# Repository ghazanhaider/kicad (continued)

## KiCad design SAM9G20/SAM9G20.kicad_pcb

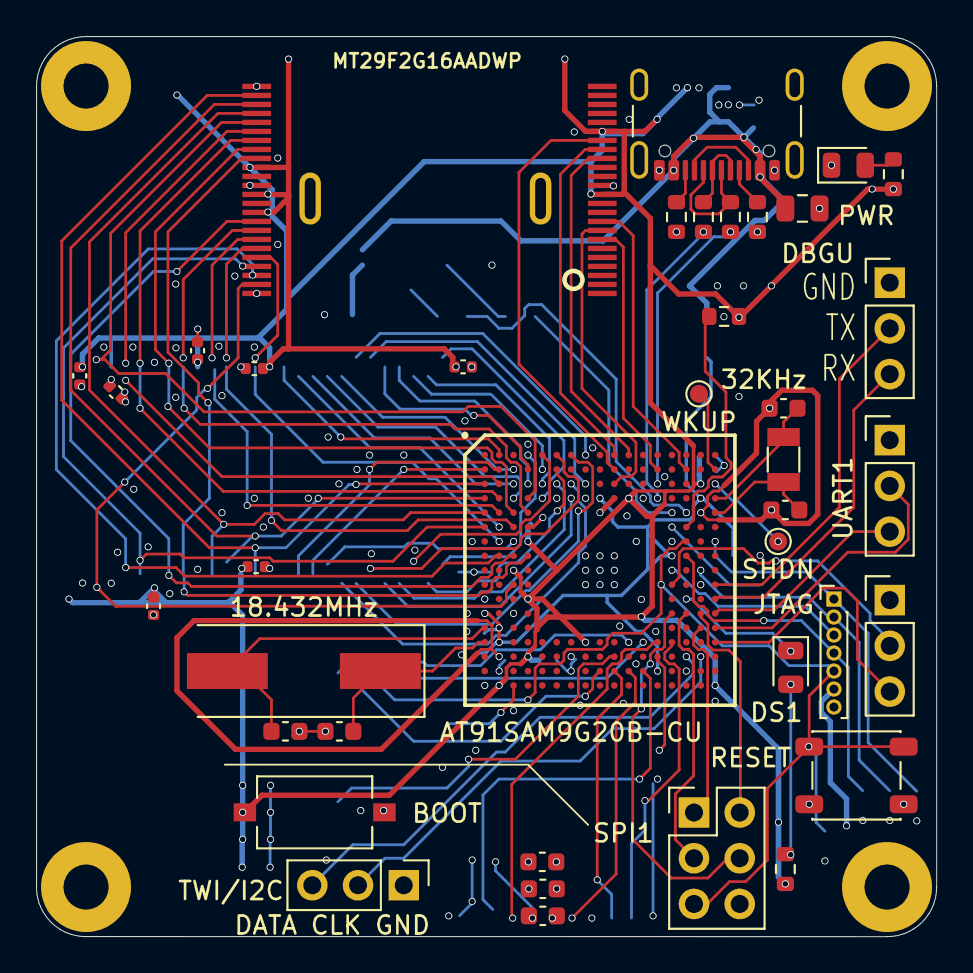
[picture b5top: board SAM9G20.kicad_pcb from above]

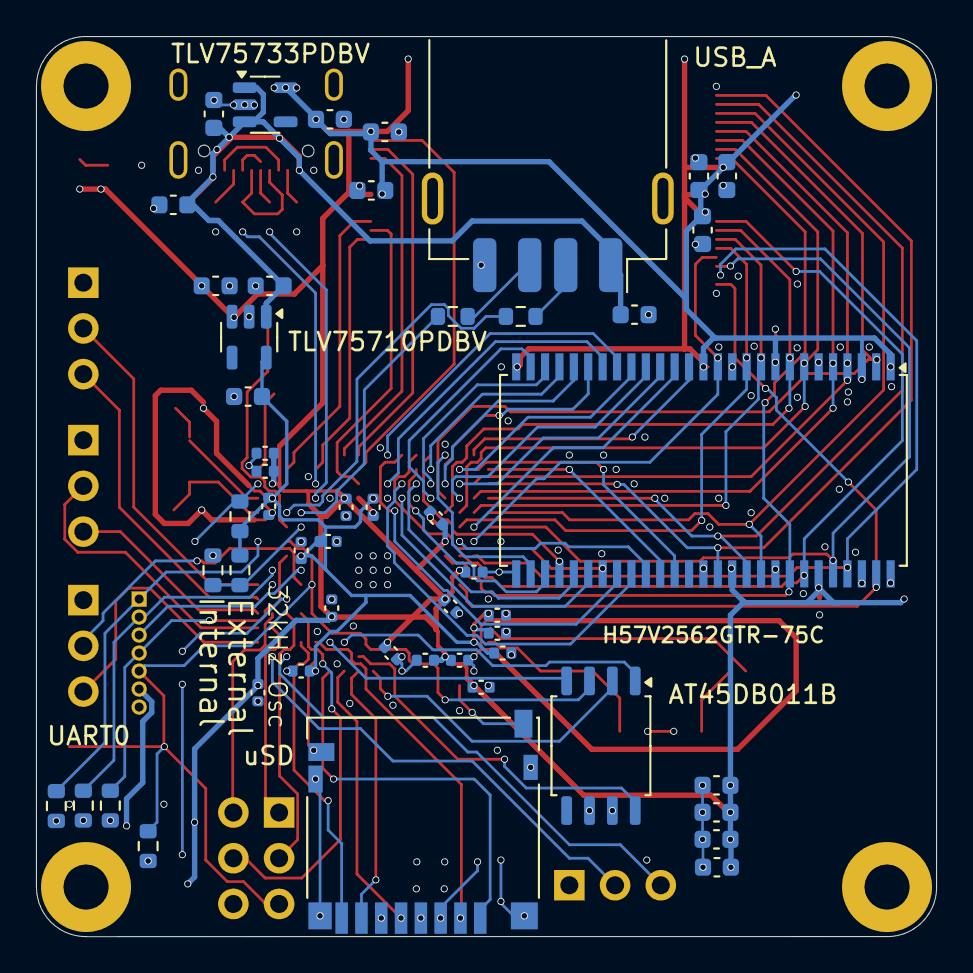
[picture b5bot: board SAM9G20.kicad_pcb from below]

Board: 4 copper layers, 50.0 x 50.0 mm, 94 parts (51 on the bottom side), 99 nets.

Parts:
C1, C2, C3, C4: 10pF; C_0603_1608Metric
C5, C6, C7, C8, C9, C10, C11, C12, C13, C14, C15, C16, C17, C18, C19, C33, C34, C35, C36, C37, C38, C39, C45: 100nF; C_0402_1005Metric
C20, C21, C22, C23: 10uF; C_0402_1005Metric
C24, C25: 1uF; C_0603_1608Metric
C26, C27: 10uF; C_0603_1608Metric
C28: 10nF; C_0603_1608Metric
C29: 47uF; C_0805_2012Metric
C30, C40, C41, C42, C43, C44, C47, C48, C49, C50, C52, C53: 100nF; C_0603_1608Metric
C31, C54: 4.7uF; C_0603_1608Metric
D1: PWR; LED_0805_2012Metric
D2: DS1; LED_0805_2012Metric
H1, H2, H3, H4: MountingHole_Pad; MountingHole_2.5mm_Pad
IC1: AT91SAM9G20B-CU; BGA217C80P17X17_1500X1500X140
J1: USB_A; USB_A_Receptacle_GCT_USB1046
J3: USB Device and Power; USB_C_Receptacle_GCT_USB4105-xx-A_16P_TopMnt_Horizontal
J4: DBGU; PinHeader_1x03_P2.54mm_Vertical
J5: uSD; microSD_HC_Hirose_DM3D-SF
J6: UART1; PinHeader_1x03_P2.54mm_Vertical
J7: UART0; PinHeader_1x03_P2.54mm_Vertical
J9: SPI1; PinHeader_2x03_P2.54mm_Vertical
J10: TWI/I2C; PinHeader_1x03_P2.54mm_Vertical
R1, R2, R3, R4: 27R; R_0603_1608Metric
R7, R10, R18: 1K; R_0603_1608Metric
R8: 470K; R_0603_1608Metric
R9, R14, R15, R16, R17: 100K; R_0603_1608Metric
R11: DNP; R_0603_1608Metric
R12, R13: 5.1K; R_0603_1608Metric
SW1: BOOT; SW_Tactile_SPST_NO_Straight_CK_PTS636Sx25SMTRLFS
SW3: RESET; SW_SPST_PTS647_Sx38
TP1: WKUP; TestPoint_Pad_D1.0mm
TP2: SHDN; TestPoint_Pad_D1.0mm
U1: H57V2562GTR-75C; TSOP-II-54_22.2x10.16mm_P0.8mm
U2: MT29F2G16AADWP; TSOP-48
U3: JTAG; PinHeader_1x07_P1.00mm_Vertical
U4: AT45DB011B; SOIC-8_5.275x5.275mm_P1.27mm
U5: TLV75710PDBV; SOT-23-5
U6: TLV75733PDBV; SOT-23-5
Y1: 18.432MHz; Crystal_SMD_HC49-SD
Y2: 32KHz; Crystal_SMD_3215-2Pin_3.2x1.5mm

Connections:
1.0V: C5.1, C6.1, C7.1, C8.1, C9.1, C10.1, C11.1, C20.1, C26.2, IC1.D9 (VDDCORE_1), IC1.D16 (VDDBU), IC1.H14 (VDDCORE_2), IC1.M1 (VDDCORE_3), IC1.N2 (VDDPLL_1), IC1.P2 (VDDPLL_2), IC1.T13 (VDDCORE_4), R8.2, R14.2, U5.5 (OUT)
3.3V: C12.1, C13.1, C14.1, C15.1, C16.1, C17.1, C18.1, C19.1, C21.1, C22.1, C23.1, C27.2, C28.2, C33.1, C34.1, C35.1, C36.1, C37.1, C38.1, C39.1, C40.1, C41.1, C42.1, C43.1, C44.1, C45.1, C47.1, C48.1, C49.1, C50.1, C52.1, C53.1, C54.1, IC1.C16 (VDDUSB), IC1.D11 (VDDIOM_1), IC1.G4 (VDDIOM_2), IC1.J3 (VDDIOM_3), IC1.L4 (VDDOSC), IC1.P8 (VDDIOP_1), IC1.R4 (VDDANA), IC1.U2 (ADVREF), IC1.U17 (VDDIOP_2), J5.4 (VDD), R7.2, R9.2, R10.2, R15.2, R16.2, R17.2, R18.2, SW1.1 (A), U1.1 (VDD), U1.3 (VDDQ), U1.9 (VDDQ), U1.14 (VDD), U1.27 (VDD), U1.43 (VDDQ), U1.49 (VDDQ), U2.12 (VCC), U2.19 (~WP), U2.34 (VCC@1), U2.37 (VCC@2), U2.39 (VCC@3), U3.6, U5.3 (EN), U6.5 (OUT)
A2: IC1.C4 (A2), U1.23 (A0)
A3: IC1.B5 (A3), U1.24 (A1)
A4: IC1.C5 (A4), U1.25 (A2)
A5: IC1.D5 (A5), U1.26 (A3)
A6: IC1.A4 (A6), U1.29 (A4)
A7: IC1.B6 (A7), U1.30 (A5)
A8: IC1.A5 (A8), U1.31 (A6)
A9: IC1.C6 (A9), U1.32 (A7)
A10: IC1.D7 (A10), U1.33 (A8)
A11: IC1.A6 (A11), U1.34 (A9)
A13: IC1.A7 (A13), U1.35 (A11)
A14: IC1.C7 (A14), U1.36 (A12)
A21: IC1.A10 (A21), U2.17 (ALE)
A22: IC1.A11 (A22), U2.16 (CLE)
BA0/A16: IC1.A8 (BA0/A16), U1.20 (BA0)
BA1/A17: IC1.C8 (BA1/A17), U1.21 (BA1)
BMS: IC1.F15 (BMS), R9.1
CAS: IC1.C3 (CAS), U1.17 (~CAS)
CFIOR/NBS1/NWR1: IC1.B2 (CFIOR/NBS1/NWR1), U1.39 (DQMH)
D0: IC1.D4 (D0), U1.2 (DQ0), U2.29 (I/O_0)
D1: IC1.C2 (D1), U1.4 (DQ1), U2.30 (I/O_1)
D2: IC1.D2, U1.5 (DQ2), U2.31 (I/O_2)
D3: IC1.E3 (D3), U1.7 (DQ3), U2.32 (I/O_3)
D4: IC1.E4 (D4), U1.8 (DQ4), U2.41 (I/O_4)
D5: IC1.E2 (D5), U1.10 (DQ5), U2.42 (I/O_5)
D6: IC1.F3 (D6), U1.11 (DQ6), U2.43 (I/O_6)
D7: IC1.G2 (D7), U1.13 (DQ7), U2.44 (I/O_7)
D8: IC1.C1 (D8), U1.42 (DQ8), U2.26 (I/O_8)
D9: IC1.D1 (D9), U1.44 (DQ9), U2.27 (I/O_9)
D10: IC1.E1 (D10), U1.45 (DQ10), U2.28 (I/O_10)
D11: IC1.H4 (D11), U1.47 (DQ11), U2.33 (I/O_11)
D12: IC1.H3 (D12), U1.48 (DQ12), U2.40 (I/O_12)
D13: IC1.F1 (D13), U1.50 (DQ13), U2.45 (I/O_13)
D14: IC1.H2 (D14), U1.51 (DQ14), U2.46 (I/O_14)
D15: IC1.K3 (D15), U1.53 (DQ15), U2.47 (I/O_15)
DDM: IC1.D13 (DDM), R1.2
DDP: IC1.C13 (DDP), R2.2
DRXD: IC1.L17 (PB14), J4.3
DTXD: IC1.K17 (PB15), J4.2
GNDANA: C1.2, C2.2, C3.2, C4.2, C5.2, C6.2, C7.2, C8.2, C9.2, C10.2, C11.2, C12.2, C13.2, C14.2, C15.2, C16.2, C17.2, C18.2, C19.2, C20.2, C21.2, C22.2, C23.2, C24.1, C25.1, C26.1, C27.1, C28.1, C29.1, C30.1, C31.1, C33.2, C34.2, C35.2, C36.2, C37.2, C38.2, C39.2, C40.2, C41.2, C42.2, C43.2, C44.2, C45.2, C47.2, C48.2, C49.2, C50.2, C52.2, C53.2, C54.2, D1.1 (K), H1.1, H2.1, H3.1, H4.1, IC1.D6 (GND_1), IC1.D8 (GND_2), IC1.D10 (GNDUSB_1), IC1.D12 (GNDUSB_2), IC1.E16 (GNDBU), IC1.F4 (GND_3), IC1.G14 (GND_4), IC1.H8 (GND_5), IC1.H9 (GND_6), IC1.H10 (GND_7), IC1.J8 (GND_8), IC1.J9 (GND_9), IC1.J10 (GND_10), IC1.K8 (GND_11), IC1.K9 (GND_12), IC1.K10 (GND_13), IC1.K16 (GND_14), IC1.L1 (GND_15), IC1.M3 (GND_16), IC1.R2 (GNDANA), IC1.R7 (GND_17), IC1.T2 (GNDPLL_1), IC1.T7 (GND_18), IC1.T15 (GND_19), IC1.U1 (GNDPLL_2), J1.4 (GND), J1.5 (Shield), J3.A1 (GND), J3.A12 (GND), J3.B1 (GND), J3.B12 (GND), J3.S1 (SHIELD), J4.1, J5.3 (VSS), J5.6 (VSS), J5.11 (WRITE_PROTECT), J6.1, J7.1, J9.6, J10.1, R11.2, R12.2, R13.2, SW3.2, U1.6 (VSSQ), U1.12 (VSSQ), U1.28 (VSS), U1.41 (VSS), U1.46 (VSSQ), U1.52 (VSSQ), U1.54 (VSS), U2.13 (VSS), U2.25 (VSS@1), U2.36 (VSS@2), U2.48 (VSS@3), U3.7, U4.7 (GND), U5.2 (GND), U6.2 (GND)
HDMA: IC1.E15 (HDMA), R4.2
HDPA: IC1.E14 (HDPA), R3.2
MCCDA: IC1.P13 (PA7), J5.2 (CMD)
MCCK: IC1.T11 (PA8), J5.5 (CLK)
MCDA0: IC1.T10 (PA6), J5.7 (DAT0)
MCDA1: IC1.P14 (PA9), J5.8 (DAT1)
MCDA2: IC1.R13 (PA10), J5.9 (DAT2)
MCDA3: IC1.T12 (PA11), J5.1 (CD/DAT3)
NANDOE: IC1.C10 (NANDOE), U2.8 (~RE)
NANDWE: IC1.B10 (NANDWE), U2.18 (~WE)
NBS0/A0: IC1.A2 (NBS0/A0), U1.15 (DQML)
NRST: IC1.G15 (NRST), J9.5, R10.1, SW3.1, U3.5, U4.3 (~RESET)
unnamed: D1.2 (A), R7.1
unnamed: D2.2 (A), R18.1
unnamed: J1.3 (D+), R3.1
unnamed: J1.2 (D-), R4.1
unnamed: J3.A5 (CC1), R12.1
unnamed: J3.B5 (CC2), R13.1
unnamed: J3.A6 (D+), J3.B6 (D+), R2.1
unnamed: J3.A7 (D-), J3.B7 (D-), R1.1
unnamed: SW1.2 (B), U4.6 (VCC)
OSCSEL: IC1.F14 (OSCSEL), R11.1, R14.1
PA0: IC1.R10 (PA0), U4.8 (SO)
PA1: IC1.P11 (PA1), U4.1 (SI)
PA2: IC1.T9 (PA2), U4.2 (SCK)
PA3: IC1.P12 (PA3), U4.4 (~CS)
PA23: IC1.R15 (PA23), J10.3
PA24: IC1.R16 (PA24), J10.2
PB0: IC1.N16 (PB0), J9.1
PB1: IC1.M14 (PB1), J9.4
PB2: IC1.M15 (PB2), J9.3
PB3: IC1.M16 (PB3), J9.2
PB4: IC1.K14 (PB4), J7.2
PB5: IC1.P17 (PB5), J7.3
PB6: IC1.N17 (PB6), J6.2
PB7: IC1.M17 (PB7), J6.3
PB9: D2.1 (K), IC1.L15 (PB9)
PC2: IC1.U3 (PC2), J5.10 (CARD_DETECT)
PC13: IC1.B13 (PC13), U2.7 (~R/B)
PC14: IC1.B15 (PC14), U2.9 (~CE)
RAS: IC1.D3 (RAS), U1.18 (~RAS)
SDA10: IC1.B4 (SDA10), U1.22 (A10)
SDCK: IC1.B1 (SDCK), U1.38 (CLK)
SDCKE: IC1.G3 (SDCKE), U1.37 (CKE)
SDCS/NCS1: IC1.B3 (SDCS/NCS1), U1.19 (~CS)
SDWE: IC1.F2 (SDWE), U1.16 (~WE)
SHDN: IC1.C17 (SHDN), R8.1, TP2.1
TCK: IC1.H15 (TCK), R17.1, U3.4
TDI: IC1.J16 (TDI), R16.1, U3.2
TDO: IC1.J14 (TDO), U3.3
TMS: IC1.G17 (TMS), R15.1, U3.1
VBUS: C24.2, C25.2, C29.2, C30.2, C31.2, J1.1 (VBUS), J3.A4 (VBUS), J3.A9 (VBUS), J3.B4 (VBUS), J3.B9 (VBUS), U5.1 (IN), U6.1 (IN), U6.3 (EN)
WKUP: IC1.B17 (WKUP), TP1.1
XIN: C1.1, IC1.N1 (XIN), Y1.2
XIN32: C3.1, IC1.D17 (XIN32), Y2.2
XOUT: C2.1, IC1.P1 (XOUT), Y1.1
XOUT32: C4.1, IC1.E17 (XOUT32), Y2.1

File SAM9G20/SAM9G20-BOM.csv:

Reference,Value,Datasheet,Footprint,Qty,DNP,,
U3,JTAG,~,,1,,,
SW3,RESET,~,Button_Switch_SMD:SW_SPST_PTS647_Sx38,1,,,
SW1,BOOT,~,Button_Switch_SMD:SW_Tactile_SPST_NO_Straight_CK_PTS636Sx25SMTRLFS,1,,KSR221GNCLFS,
"C5,C6,C7,C8,C9,C10,C11,C12,C13,C14,C15,C16,C17,C18,C19,C33,C34,C35,C36,C37,C38,C39,C45",100nF,~,Capacitor_SMD:C_0402_1005Metric,23,,,
"C20,C21,C22,C23",10uF,~,Capacitor_SMD:C_0402_1005Metric,4,,,
"C1,C2,C3,C4",10pF,~,Capacitor_SMD:C_0603_1608Metric,4,,only 9,100
"C24,C25",1uF,~,Capacitor_SMD:C_0603_1608Metric,2,,,
"C26,C27",10uF,~,Capacitor_SMD:C_0603_1608Metric,2,,,100
C28,10nF,~,Capacitor_SMD:C_0603_1608Metric,1,,,
"C30,C40,C41,C42,C43,C44,C47,C48,C49,C50,C52,C53",100nF,~,Capacitor_SMD:C_0603_1608Metric,12,,only 23,100
"C31,C54",4.7uF,~,Capacitor_SMD:C_0603_1608Metric,2,,,
C29,47uF,~,Capacitor_SMD:C_0805_2012Metric,1,,only 7 found,
J5,SD_Card_Receptacle,http://portal.fciconnect.com/Comergent//fci/drawing/10067847.pdf,Connector_Card:microSD_HC_Hirose_DM3D-SF,1,,only 3 found,10
J4,DBGU,~,Connector_PinHeader_2.54mm:PinHeader_1x03_P2.54mm_Vertical,1,,,
J6,UART1,~,Connector_PinHeader_2.54mm:PinHeader_1x03_P2.54mm_Vertical,1,,,
J7,UART0,~,Connector_PinHeader_2.54mm:PinHeader_1x03_P2.54mm_Vertical,1,,,
J10,TWI,~,Connector_PinHeader_2.54mm:PinHeader_1x03_P2.54mm_Vertical,1,,,
J9,SPI1,~,Connector_PinHeader_2.54mm:PinHeader_2x03_P2.54mm_Vertical,1,,,
J1,USB_A,~,Connector_USB:USB_A_Receptacle_GCT_USB1046,1,,only 3 found,
J3,USB Device and Power,https://www.usb.org/sites/default/files/documents/usb_type-c.zip,Connector_USB:USB_C_Receptacle_GCT_USB4105-xx-A_16P_TopMnt_Horizontal,1,,,10
Y2,32.768kHz,ECS-.327-12.5-34B-TR,Crystal:Crystal_SMD_3215-2Pin_3.2x1.5mm,1,,,
Y1,18.432MHz,ABLS-18.432MHZ-B2-T,Crystal:Crystal_SMD_HC49-SD,1,,,
IC1,AT91SAM9G20B-CU,http://www.microchip.com/mymicrochip/filehandler.aspx?ddocna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,GhazanCustom:BGA217C80P17X17_1500X1500X140,1,,,
U2,MT29F2G16AADWP,,GhazanCustom:TSOP-48,1,,only 5,
D1,PWR,LTST-S220GKT,LED_SMD:LED_0805_2012Metric,1,,,
D2,DS1,LTST-S220GKT,LED_SMD:LED_0805_2012Metric,1,,,
U4,AT45DB011B-SU,,Package_SO:SOIC-8_5.275x5.275mm_P1.27mm,1,,,
U1,H57V2562GTR-75C,,Package_SO:TSOP-II-54_22.2x10.16mm_P0.8mm,1,,,
U5,TLV75710PDBV,https://www.ti.com/lit/ds/symlink/tlv757p.pdf,Package_TO_SOT_SMD:SOT-23-5,1,,,
U6,TLV75733PDBV,https://www.ti.com/lit/ds/symlink/tlv757p.pdf,Package_TO_SOT_SMD:SOT-23-5,1,,,
"R1,R2,R3,R4",27R,~,Resistor_SMD:R_0603_1608Metric,4,,,100
"R7,R10,R18",1K,~,Resistor_SMD:R_0603_1608Metric,3,,,100
R8,470K,~,Resistor_SMD:R_0603_1608Metric,1,,,
"R9,R14,R15,R16,R17",100K,~,Resistor_SMD:R_0603_1608Metric,5,,,
R11,DNP,~,Resistor_SMD:R_0603_1608Metric,1,,,
"R12,R13",5.1K,~,Resistor_SMD:R_0603_1608Metric,2,,,
TP1,WKUP,~,TestPoint:TestPoint_Pad_D1.0mm,1,,,
TP2,SHDN,~,TestPoint:TestPoint_Pad_D1.0mm,1,,,

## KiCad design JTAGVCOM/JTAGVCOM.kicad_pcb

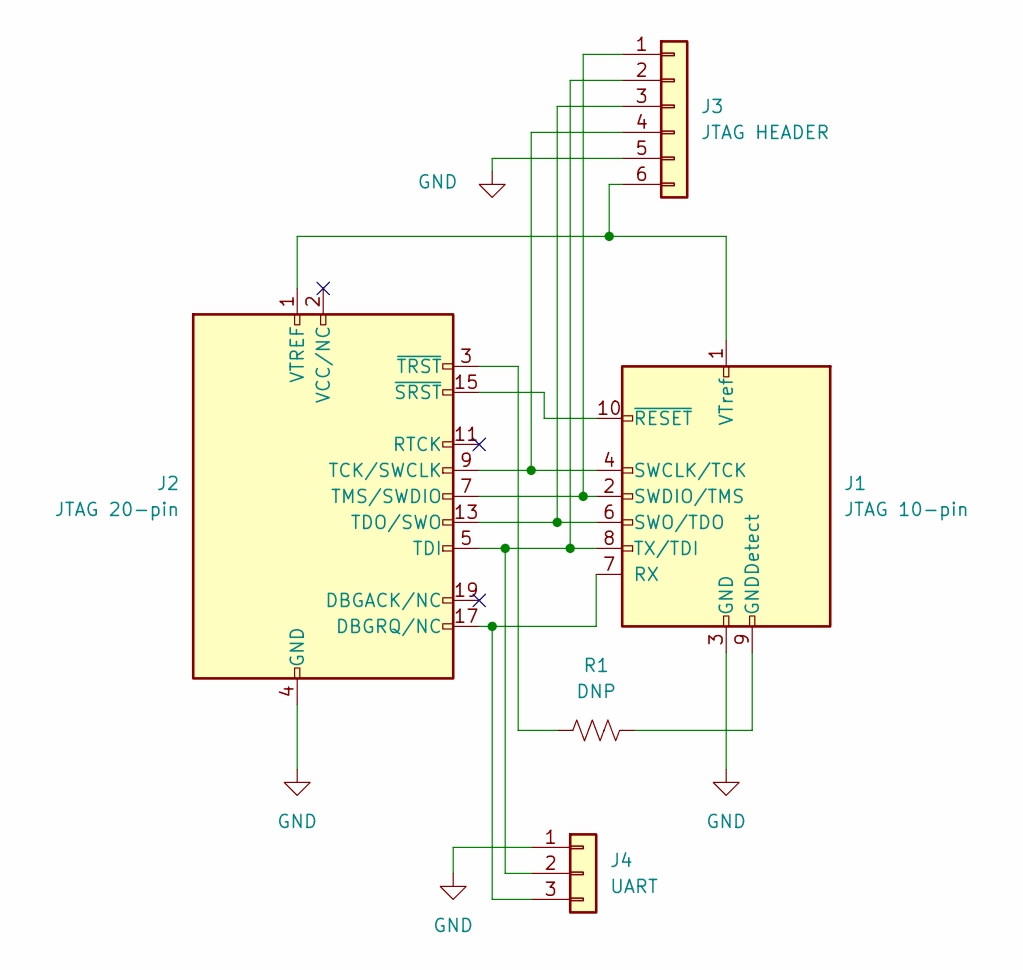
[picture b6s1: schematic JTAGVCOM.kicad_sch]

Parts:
J1: JTAG 10-pin; PinHeader_2x05_P1.27mm_Vertical
J2: JTAG 20-pin; PinHeader_2x10_P2.54mm_Vertical
J3: JTAG HEADER; PinHeader_1x06_P2.54mm_Vertical
J4: UART; PinHeader_1x03_P2.54mm_Vertical
R1: DNP; R_0805_2012Metric_Pad1.20x1.40mm_HandSolder

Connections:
GND: J1.3 (GND), J1.5 (GND), J2.4 (GND), J2.6 (GND), J2.8 (GND), J2.10 (GND), J2.12 (GND), J2.14 (GND), J2.16 (GND), J2.18 (GND), J2.20 (GND), J3.5, J4.1
unnamed: J1.9 (GNDDetect), R1.2
unnamed: J1.7 (RX), J2.17 (DBGRQ/NC), J4.3
unnamed: J1.4 (SWCLK/TCK), J2.9 (TCK/SWCLK), J3.4
unnamed: J1.2 (SWDIO/TMS), J2.7 (TMS/SWDIO), J3.1
unnamed: J1.6 (SWO/TDO), J2.13 (TDO/SWO), J3.3
unnamed: J1.8 (TX/TDI), J2.5 (TDI), J3.2, J4.2
unnamed: J1.1 (VTref), J2.1 (VTREF), J3.6
unnamed: J1.10 (~RESET), J2.15 (~SRST)
unnamed: J2.3 (~TRST), R1.1

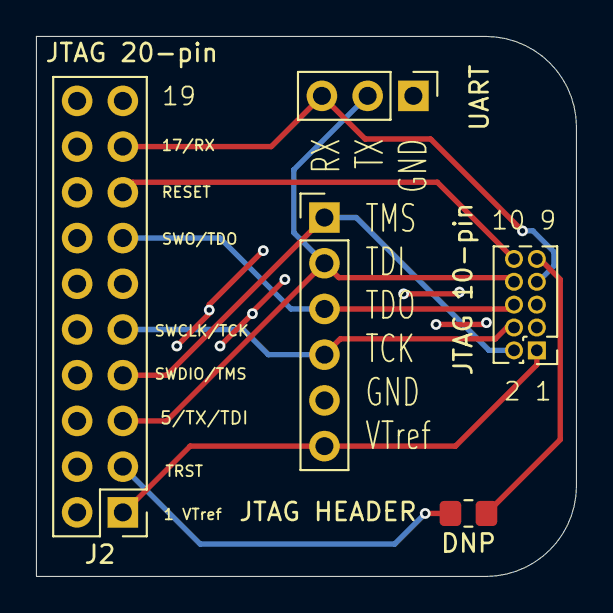
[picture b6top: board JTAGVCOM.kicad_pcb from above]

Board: 2 copper layers, 30.0 x 30.0 mm, 5 parts (0 on the bottom side), 10 nets.

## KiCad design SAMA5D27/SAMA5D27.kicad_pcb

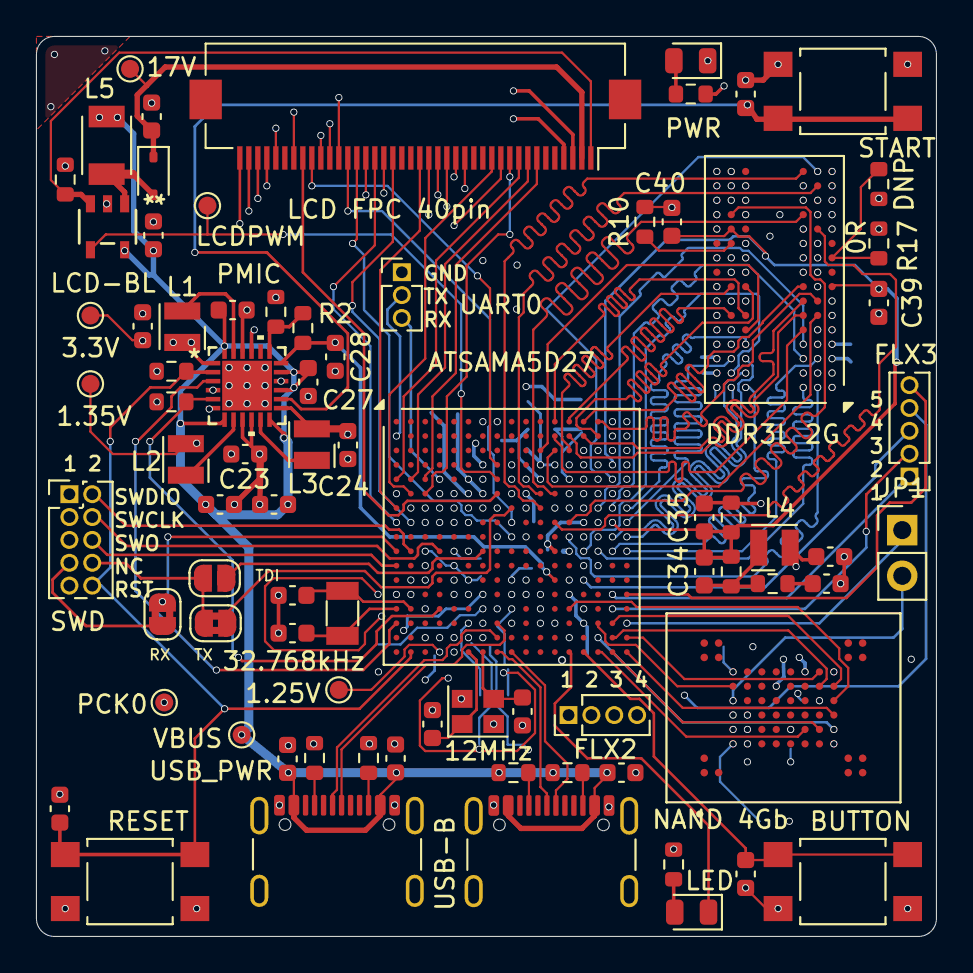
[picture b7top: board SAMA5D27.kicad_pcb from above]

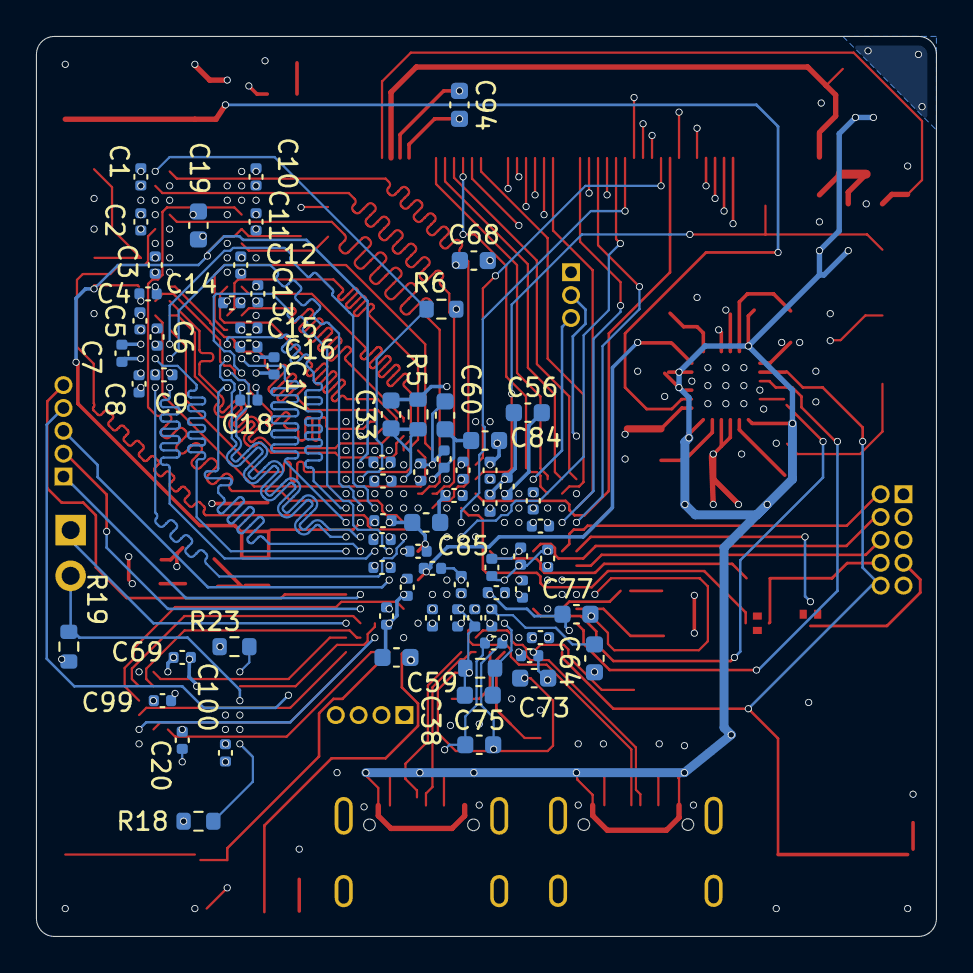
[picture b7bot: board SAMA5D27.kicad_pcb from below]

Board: 6 copper layers, 50.0 x 50.0 mm, 152 parts (73 on the bottom side), 151 nets.

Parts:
C1, C2, C3, C4, C5, C6, C7, C8, C9, C10, C11, C12, C13, C14, C15, C16, C17, C18, C20, C41, C42, C43, C44, C45, C46, C47, C48, C49, C50, C51, C52, C53, C54, C55, C57, C58, C62, C63, C65, C67, C69, C71, C72, C74, C76, C78, C79, C83, C87, C89, C91, C99, C100: 100nF; C_0402_1005Metric
C19, C56, C59, C64, C68, C73, C75, C77, C84, C85, C92, C93: 1uF; C_0603_1608Metric
C21, C23, C24: 22uF; C_0603_1608Metric
C22, C25, C26, C27, C28, C36, C37, C80, C81, C94, C97: 4.7uF; C_0603_1608Metric
C29, C30, C31, C32: 16pF; C_0603_1608Metric
C33: 22pF; C_0603_1608Metric
C34, C35, C39, C40, C95, C96, C98: 100nF; C_0603_1608Metric
C38: 10pF; C_0603_1608Metric
C60: 10nF; C_0603_1608Metric
D1: D_Schottky; D_SOD-323
D2: LED; LED_0805_2012Metric
D3: PWR; LED_0805_2012Metric
IC1: D1216ECMDXGJD-U; Micron_FBGA-96_7.5x13.5mm_Layout9x16_P0.8mm
J1: LCD FPC 40pin; Hirose_FH12-40S-0.5SH_1x40-1MP_P0.50mm_Horizontal
J2: SWD; PinHeader_2x05_P1.27mm_Vertical
J3: UART0; PinHeader_1x03_P1.27mm_Vertical
J5: FLX2; PinHeader_1x04_P1.27mm_Vertical
J6: FLX3; PinHeader_1x05_P1.27mm_Vertical
JP1: BOOT; PinHeader_1x02_P2.54mm_Vertical
JP2: Jumper_2_Small_Open; SolderJumper-2_P1.3mm_Open_RoundedPad1.0x1.5mm
JP3, JP4: Jumper_2_Small_Bridged; SolderJumper-2_P1.3mm_Bridged2Bar_RoundedPad1.0x1.5mm
L1, L2, L3: 2.2uH; L_Wurth_WE-LQSH-2512
L4: 10uH 150mA; L_Wurth_WE-LQSH-2512
L5: 15uH; L_TDK_NLV32_3.2x2.5mm
P1: USB_PWR; USB_C_Receptacle_GCT_USB4105-xx-A_16P_TopMnt_Horizontal
P2: USB-B; USB_C_Receptacle_GCT_USB4105-xx-A_16P_TopMnt_Horizontal
R1: 182k 1%; R_0603_1608Metric
R2: 324k 1%; R_0603_1608Metric
R3, R4, R6: 100k; R_0603_1608Metric
R5: 23.2k 1%; R_0603_1608Metric
R7, R8: 6.8k 1%; R_0603_1608Metric
R9: 1R 1%; R_0603_1608Metric
R10: 240R 1%; R_0603_1608Metric
R11, R12: 5.1k 1%; R_0603_1608Metric
R13, R14: 56k 1%; R_0603_1608Metric
R15: 5.62k 1%; R_0603_1608Metric
R16: DNP; R_0603_1608Metric
R17: 0R; R_0603_1608Metric
R18, R19: 470k; R_0603_1608Metric
R20: 6.3; R_0603_1608Metric
R21, R22, R23: 1k; R_0603_1608Metric
SW1: BUTTON; SW_SPST_TL3305A
SW2: START; SW_SPST_TL3305A
SW3: RESET; SW_SPST_TL3305A
TP1: VBUS; TestPoint_Pad_D1.0mm
TP2: 3.3V; TestPoint_Pad_D1.0mm
TP3: 1.35V; TestPoint_Pad_D1.0mm
TP4: 1.25V; TestPoint_Pad_D1.0mm
TP5: PCK0; TestPoint_Pad_D1.0mm
TP6: 17V; TestPoint_Pad_D1.0mm
TP7: LCDPWM; TestPoint_Pad_D1.0mm
U1: LCD-BL; TSOT-23-5_D5_MCH
U2: PMIC; VQFN24_RMB_MCH
U3: MT29F4G08ABAFAH4-IT:F; BGA63C80P10X12_1050X1300X100N
U5: ATSAMA5D27; LFBGA-289_14x14mm_Layout17x17_P0.8mm
Y1: 12MHz; Crystal_SMD_2520-4Pin_2.5x2.0mm
Y2: 32.768kHz; Crystal_SMD_3215-2Pin_3.2x1.5mm

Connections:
+1V25: C24.2, C48.1, C49.1, C50.1, C51.1, C52.1, C53.1, C62.2, C64.2, C71.1, C72.1, C73.1, C84.1, L3.1, TP4.1, U2.13 (OUT3), U5.D7 (VDDCORE), U5.D9 (VDDCORE), U5.H3 (VDDCORE), U5.K13 (VDDCORE), U5.N5 (VDDCORE), U5.N9 (VDDCORE), U5.P7 (VDDUTMIC), U5.R9 (VDDHSIC), U5.U4 (VDDPLLA)
+2V5: C28.1, C89.1, R2.2, U2.18 (LOUT), U5.M12 (VDDFUSE)
+3V3: C20.2, C21.1, C54.1, C55.1, C56.1, C57.1, C58.1, C59.1, C63.1, C65.2, C67.2, C69.2, C74.1, C75.1, C76.1, C77.1, C78.1, C79.1, C83.1, C85.1, C87.1, C91.2, C94.2, C99.2, C100.2, J1.4, J2.1 (VTref), L1.2, R3.2, R4.2, R18.1, R19.2, R21.1, R22.1, R23.2, TP2.1, U2.1 (OUT1), U2.21 (LEN), U3.D3 (VCC), U3.G4 (VCC), U3.H8 (VCC), U3.J6 (VCC), U5.E6 (VDDIOP0), U5.F4 (VDDISC), U5.F7 (VDDIOP0), U5.F10 (VDDIOP2), U5.K3 (VDDANA), U5.L5 (VDDANA), U5.M6 (ADVREFP), U5.N7 (VDDBU), U5.N13 (VDDIOP1), U5.P8 (VDDUTMII), U5.P11 (VDDSDMMC), U5.R14 (VDDIOP1), U5.T3 (VDDAUDIOPLL), U5.T7 (VDDOSC)
/NAND/NAND_CE: JP1.2 (B), R19.1, U3.C6 (CE#)
DDR_A0: IC1.N3 (A0), U5.F12 (DDR_A0)
DDR_A1: IC1.P7 (A1), U5.C17 (DDR_A1)
DDR_A2: IC1.P3 (A2), U5.B17 (DDR_A2)
DDR_A3: IC1.N2 (A3), U5.B16 (DDR_A3)
DDR_A4: IC1.P8 (A4), U5.C16 (DDR_A4)
DDR_A5: IC1.P2 (A5), U5.G14 (DDR_A5)
DDR_A6: IC1.R8 (A6), U5.F14 (DDR_A6)
DDR_A7: IC1.R2 (A7), U5.F11 (DDR_A7)
DDR_A8: IC1.T8 (A8), U5.C14 (DDR_A8)
DDR_A9: IC1.R3 (A9), U5.D13 (DDR_A9)
DDR_A10: IC1.L7 (A10/AP), U5.C15 (DDR_A10)
DDR_A11: IC1.R7 (A11), U5.A16 (DDR_A11)
DDR_A12: IC1.N7 (A12/BC#), U5.A17 (DDR_A12)
DDR_A13: IC1.T3 (A13), U5.G11 (DDR_A13)
DDR_BA0: IC1.M2 (BA0), U5.H12 (DDR_BA0)
DDR_BA1: IC1.N8 (BA1), U5.H13 (DDR_BA1)
DDR_BA2: IC1.M3 (BA2), U5.F17 (DDR_BA2)
DDR_CAL: C33.1, R5.2, U5.E13 (DDR_CAL)
DDR_CAS: IC1.K3 (CAS#), U5.G12 (DDR_CAS)
DDR_CKE: IC1.K9 (CKE), U5.F16 (DDR_CKE)
DDR_CLKN: IC1.K7 (CK#), U5.D17 (DDR_CLKN)
DDR_CLKP: IC1.J7 (CK), U5.E17 (DDR_CLK)
DDR_CS: IC1.L2 (CS#), U5.G13 (DDR_CS)
DDR_D0: IC1.E3 (DQL0), U5.B12 (DDR_D0)
DDR_D1: IC1.F7 (DQL1), U5.A12 (DDR_D1)
DDR_D2: IC1.F2 (DQL2), U5.C12 (DDR_D2)
DDR_D3: IC1.F8 (DQL3), U5.A13 (DDR_D3)
DDR_D4: IC1.H3 (DQL4), U5.A14 (DDR_D4)
DDR_D5: IC1.H8 (DQL5), U5.C13 (DDR_D5)
DDR_D6: IC1.G2 (DQL6), U5.A15 (DDR_D6)
DDR_D7: IC1.H7 (DQL7), U5.B15 (DDR_D7)
DDR_D8: IC1.D7 (DQU0), U5.G17 (DDR_D8)
DDR_D9: IC1.C3 (DQU1), U5.G16 (DDR_D9)
DDR_D10: IC1.C8 (DQU2), U5.H17 (DDR_D10)
DDR_D11: IC1.C2 (DQU3), U5.K17 (DDR_D11)
DDR_D12: IC1.A7 (DQU4), U5.K16 (DDR_D12)
DDR_D13: IC1.A2 (DQU5), U5.J13 (DDR_D13)
DDR_D14: IC1.B8 (DQU6), U5.K14 (DDR_D14)
DDR_D15: IC1.A3 (DQU7), U5.K15 (DDR_D15)
DDR_DQM0: IC1.E7 (DML), U5.C11 (DDR_DQM0)
DDR_DQM1: IC1.D3 (DMU), U5.G15 (DDR_DQM1)
DDR_DQS0N: IC1.G3 (DQSL#), U5.B14 (DDR_DQSN0)
DDR_DQS0P: IC1.F3 (DQSL), U5.B13 (DDR_DQS0)
DDR_DQS1N: IC1.B7 (DQSU#), U5.J16 (DDR_DQSN1)
DDR_DQS1P: IC1.C7 (DQSU), U5.J17 (DDR_DQS1)
DDR_RAS: IC1.J3 (RAS#), U5.F13 (DDR_RAS)
DDR_RESETN: IC1.T2 (RESET#), R6.1, U5.E16 (DDR_RESETN)
DDR_VREF: C34.2, C35.1, C39.1, C40.1, IC1.H1 (VREFDQ), IC1.M8 (VREFCA), R7.1, R8.2, U5.D16 (DDR_VREF), U5.H16 (DDR_VREF)
DDR_WE: IC1.L3 (WE#), U5.F15 (DDR_WE)
FLEXCOM2_IO0: J5.1, U5.R12 (PA6)
FLEXCOM2_IO1: J5.2, U5.T13 (PA7)
FLEXCOM2_IO2: J5.3, U5.N10 (PA8)
FLEXCOM2_IO3: J5.4, U5.N11 (PA9)
FLEXCOM3_IO0: J6.1, U5.N16 (PA15)
FLEXCOM3_IO1: J6.2, U5.P16 (PA13)
FLEXCOM3_IO2: J6.3, U5.M14 (PA14)
FLEXCOM3_IO3: J6.4, U5.M10 (PA16)
FLEXCOM3_IO4: J6.5, U5.N17 (PA17)
GND: C1.1, C2.1, C3.1, C4.1, C5.1, C6.1, C7.1, C8.1, C9.1, C10.1, C11.1, C12.1, C13.1, C14.1, C15.1, C16.1, C17.1, C18.1, C19.1, C20.1, C21.2, C22.2, C23.2, C24.1, C25.2, C26.1, C27.2, C28.2, C29.1, C30.1, C31.2, C32.2, C33.2, C35.2, C36.2, C37.2, C38.2, C39.2, C40.2, C41.2, C42.2, C43.2, C44.2, C45.2, C46.2, C47.2, C48.2, C49.2, C50.2, C51.2, C52.2, C53.2, C54.2, C55.2, C56.2, C57.2, C58.2, C59.2, C60.2, C62.1, C63.2, C64.1, C65.1, C67.1, C68.2, C69.1, C71.2, C72.2, C73.2, C74.2, C75.2, C76.2, C77.2, C78.2, C79.2, C80.2, C81.2, C83.2, C84.2, C85.2, C87.2, C89.2, C91.1, C92.2, C93.2, C94.1, C95.2, C96.2, C97.2, C98.2, C99.1, C100.1, D3.1 (K), IC1.A9 (VSS_1), IC1.B1 (VSSQ_1), IC1.B3 (VSS_2), IC1.B9 (VSSQ_2), IC1.D1 (VSSQ_3), IC1.D8 (VSSQ_4), IC1.E1 (VSS_3), IC1.E2 (VSSQ_5), IC1.E8 (VSSQ_6), IC1.F9 (VSSQ_7), IC1.G1 (VSSQ_8), IC1.G8 (VSS_4), IC1.G9 (VSSQ_9), IC1.J2 (VSS_5), IC1.J8 (VSS_6), IC1.M1 (VSS_7), IC1.M9 (VSS_8), IC1.P1 (VSS_9), IC1.P9 (VSS_10), IC1.T1 (VSS_11), IC1.T9 (VSS_12), J1.3, J1.29, J1.36, J2.3 (GND), J2.5 (GND), J2.9 (GNDDetect), J3.1, P1.A1 (GND), P1.A12 (GND), P1.B1 (GND), P1.B12 (GND), P1.S1 (SHIELD), P2.A1 (GND), P2.A12 (GND), P2.B1 (GND), P2.B12 (GND), P2.S1 (SHIELD), R1.2, R5.1, R8.1, R10.2, R11.1, R12.1, R15.1, R17.2, R20.2, SW1.1, SW2.1, SW3.1, U1.2 (GND), U2.4 (LPM), U2.9 (PGND2), U2.10 (PGND3), U2.16 (SGND), U2.22 (PGND1), U2.25 (GND), U3.C5 (VSS), U3.F7 (VSS), U3.K3 (VSS), U3.K8 (VSS), U5.D14 (GNDIODDR), U5.E7 (GNDCORE), U5.E9 (GNDCORE), U5.E11 (GNDIODDR)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
HHSDMA: P1.A7 (D-), U5.R8 (HHSDMA)
HHSDMB: P2.A7 (D-), U5.U9 (HHSDMB)
HHSDPA: P1.A6 (D+), U5.T8 (HHSDPA)
HHSDPB: P2.A6 (D+), U5.U8 (HHSDPB)
JTAG_TCK: J2.4 (SWCLK/TCK), U5.K4 (PD14)
JTAG_TDI: JP2.2 (B), U5.K7 (PD15)
JTAG_TDO: J2.6 (SWO/TDO), U5.L1 (PD16)
JTAG_TMS: J2.2 (SWDIO/TMS), U5.K2 (PD17)
LCDDAT2: J1.7, U5.E3 (PC10)
LCDDAT3: J1.8, U5.E2 (PC11)
LCDDAT4: J1.9, U5.E1 (PC12)
LCDDAT5: J1.10, U5.F3 (PC13)
LCDDAT6: J1.11, U5.F5 (PC14)
LCDDAT7: J1.12, U5.F2 (PC15)
LCDDAT10: J1.15, U5.G6 (PC16)
LCDDAT11: J1.16, U5.F1 (PC17)
LCDDAT12: J1.17, U5.H6 (PC18)
LCDDAT13: J1.18, U5.G2 (PC19)
LCDDAT14: J1.19, U5.G3 (PC20)
LCDDAT15: J1.20, U5.G1 (PC21)
LCDDAT18: J1.23, U5.H2 (PC22)
LCDDAT19: J1.24, U5.G5 (PC23)
LCDDAT20: J1.25, U5.H1 (PC24)
LCDDAT21: J1.26, U5.H5 (PC25)
LCDDAT22: J1.27, U5.J9 (PC26)
LCDDAT23: J1.28, U5.H9 (PC27)
LCDDEN: J1.34, U5.E10 (PD1)
LCDDISP: J1.31, U5.G8 (PC29)
LCDHSYNC: J1.32, U5.D8 (PC31)
LCDPCK: J1.30, U5.G10 (PD0)
LCDPWM: TP7.1, U1.4 (EN), U5.E8 (PC28)
LCDVSYNC: J1.33, U5.F8 (PC30)
LCD_ADC_XL: J1.39, U5.N2 (PD26)
LCD_ADC_XR: J1.37, U5.M3 (PD23)
LCD_ADC_YB: J1.38, U5.M2 (PD20)
LCD_ADC_YT: J1.40, U5.N1 (PD21)
NANDALE: U3.C4 (ALE), U5.J8 (PB0)
NANDCLE: U3.D5 (CLE), U5.A8 (PB1)
NANDCS3: JP1.1 (A), U5.R17 (PA31)
NANDOE: U3.D4 (RE#), U5.A7 (PB2)
NANDRDY: R23.1, U3.C8 (R/B#), U5.J10 (PC8)
NANDWE: U3.C7 (WE#), U5.R15 (PA30)
NAND_D0: U3.H4 (I/O0), U5.U15 (PA22)
NAND_D1: U3.J4 (I/O1), U5.U16 (PA23)
NAND_D2: U3.K4 (I/O2), U5.T15 (PA24)
NAND_D3: U3.K5 (I/O3), U5.U17 (PA25)
NAND_D4: U3.K6 (I/O4), U5.P13 (PA26)
NAND_D5: U3.J7 (I/O5), U5.T16 (PA27)
NAND_D6: U3.K7 (I/O6), U5.R16 (PA28)
NAND_D7: U3.J8 (I/O7), U5.T17 (PA29)
NRST: C96.1, J2.10 (~RESET), R3.1, SW3.2, U2.2 (nRSTO), U5.U2 (NRST)
unnamed: C34.1, L4.2, R7.2, R9.1
unnamed: C37.1, R9.2
unnamed: D1.2 (A), L5.2, U1.1 (SW)
unnamed: C93.1, D1.1 (K), J1.2, TP6.1
unnamed: D2.2 (A), R21.2
unnamed: D3.2 (A), R22.2
unnamed: IC1.K1 (ODT), R16.1, R17.1
unnamed: IC1.L8 (ZQ), R10.1
unnamed: J1.1, R20.1, U1.3 (FB)
unnamed: J2.7 (RX), JP4.1 (A)
unnamed: J2.8 (TX/TDI), JP2.1 (A), JP3.1 (A)
unnamed: P1.A5 (CC), R11.2
unnamed: P1.B5 (VCONN), R12.2
unnamed: P2.A5 (CC), R13.2
unnamed: P2.B5 (VCONN), R14.2
unnamed: R1.1, R2.1, U2.19 (LFB)
unnamed: L1.1, U2.23 (SW1)
unnamed: L2.2, U2.8 (SW2)
unnamed: L3.2, U2.11 (SW3)
unnamed: R18.2, U3.C3 (WP#)
PA10: D2.1 (K), U5.U13 (PA10)
PA18: C98.1, SW1.2, U5.U14 (PA18)
PB26: J3.3, U5.E4 (PB26)
PB27: J3.2, U5.B1 (PB27)
PCK0: TP5.1, U5.K6 (PD19)
PD2: JP3.2 (B), U5.G9 (PD2)
PD3: JP4.2 (B), U5.K1 (PD3)
SHDN: U2.3 (PWRHLD), U5.R1 (SHDN)
START: C95.1, SW2.2, U2.14 (nSTRT)
VBG: C38.1, R15.2, U5.R6 (VBG)
VBUS: C22.1, C25.1, C26.2, C27.1, C80.1, C81.1, C92.1, C97.1, L5.1, P1.A4 (VBUS), P1.A9 (VBUS), P1.B4 (VBUS), P1.B9 (VBUS), P2.A4 (VBUS), P2.A9 (VBUS), P2.B4 (VBUS), P2.B9 (VBUS), R13.1, R14.1, TP1.1, U1.5 (VIN), U2.7 (PVIN2), U2.12 (PVIN3), U2.15 (SELV3), U2.17 (VIN), U2.24 (PVIN1)
VDDIODDR: C1.2, C2.2, C3.2, C4.2, C5.2, C6.2, C7.2, C8.2, C9.2, C10.2, C11.2, C12.2, C13.2, C14.2, C15.2, C16.2, C17.2, C18.2, C19.2, C23.1, C36.1, C41.1, C42.1, C43.1, C44.1, C45.1, C46.1, C47.1, C60.1, C68.1, IC1.A1 (VDDQ_1), IC1.A8 (VDDQ_2), IC1.B2 (VDD_1), IC1.C1 (VDDQ_3), IC1.C9 (VDDQ_4), IC1.D2 (VDDQ_5), IC1.D9 (VDD_2), IC1.E9 (VDDQ_6), IC1.F1 (VDDQ_7), IC1.G7 (VDD_3), IC1.H2 (VDDQ_8), IC1.H9 (VDDQ_9), IC1.K2 (VDD_4), IC1.K8 (VDD_5), IC1.N1 (VDD_6), IC1.N9 (VDD_7), IC1.R1 (VDD_8), IC1.R9 (VDD_9), L2.1, L4.1, R6.2, R16.2, TP3.1, U2.6 (OUT2), U5.D11 (VDDIODDR), U5.D12 (VDDIODDR), U5.D15 (VDDIODDR), U5.E15 (VDDIODDR), U5.H15 (VDDIODDR), U5.J15 (VDDIODDR), U5.L15 (VDDIODDR)
WKUP: R4.1, U2.5 (nSTRTO), U5.P4 (WKUP)
XIN: C29.2, U5.U7 (XIN), Y1.3
XIN32: C32.1, U5.P1 (XIN32), Y2.2
XOUT: C30.2, U5.U6 (XOUT), Y1.1
XOUT32: C31.1, U5.P2 (XOUT32), Y2.1

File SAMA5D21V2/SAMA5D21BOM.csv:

"Reference","Value","Datasheet","Footprint","Qty","DNP"
"C1,C2,C3,C4,C5,C6,C7,C8,C9,C10,C11,C12,C13,C14,C15,C16,C17,C18,C38,C41,C42,C43,C44,C45,C46,C47,C48,C49,C50,C51,C52,C53,C54,C55,C57,C58,C67,C72,C74,C76,C78,C79","100nF","~","Capacitor_SMD:C_0201_0603Metric","42",""
"C19,C37,C68","1uF","-- mixed values --","Capacitor_SMD:C_0603_1608Metric","3",""
"C20,C69,C99,C100","100nF","~","Capacitor_SMD:C_0402_1005Metric","4",""
"C21,C23,C24","22uF","~C1608X5R1A226M080AC","Capacitor_SMD:C_0603_1608Metric","3",""
"C22,C25,C26,C27,C28,C36,C39,C80,C81,C97","4.7uF","-- mixed values --","Capacitor_SMD:C_0603_1608Metric","10",""
"C29,C30,C31,C32","16pF","","Capacitor_SMD:C_0603_1608Metric","4",""
"C33","22pF","~","Capacitor_SMD:C_0603_1608Metric","1",""
"C34,C35,C40,C61,C63,C64,C65,C66,C70,C71,C95,C96","100nF","~","Capacitor_SMD:C_0603_1608Metric","12",""
"C56,C59,C62,C73,C75,C77,C84","1uF","~","Capacitor_SMD:C_0201_0603Metric","7",""
"C60","10nF","~","Capacitor_SMD:C_0201_0603Metric","1",""
"D1","1N5819HW-7-F","~","Diode_SMD:D_SOD-123","1",""
"D2","LED","~","LED_SMD:LED_0805_2012Metric","1",""
"D3","PWR","~","LED_SMD:LED_0805_2012Metric","1",""
"IC1","D1216ECMDXGJD-U","D1216ECMDXGJD-U BGA96C80P9X16_900X1300X120","Package_BGA:Micron_FBGA-96_7.5x13.5mm_Layout9x16_P0.8mm","1",""
"J1","Conn_01x40","~","Connector_FFC-FPC:Hirose_FH12-40S-0.5SH_1x40-1MP_P0.50mm_Horizontal","1",""
"J8","SWD","http://infocenter.arm.com/help/topic/com.arm.doc.ddi0314h/DD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","Connector_PinHeader_1.27mm:PinHeader_2x05_P1.27mm_Vertical","1",""
"J10","UART0","~","Connector_PinHeader_1.27mm:PinHeader_1x03_P1.27mm_Vertical","1",""
"JP1","BOOT","~","Button_Switch_SMD:SW_SPST_REED_CT05-XXXX-G1","1",""
"L1,L2,L3","2.2uH","DFE252012P-2R2M=P2","Inductor_SMD_Wurth:L_Wurth_WE-LQSH-2512","3",""
"L4","10uH","DFE252012P-2R2M=P2","Inductor_SMD_Wurth:L_Wurth_WE-LQSH-2512","1",""
"P1","USB_PWR","https://www.usb.org/sites/default/files/documents/usb_type-c.zip","Connector_USB:USB_C_Receptacle_GCT_USB4105-xx-A_16P_TopMnt_Horizontal","1",""
"P2","USB-B","https://www.usb.org/sites/default/files/documents/usb_type-c.zip","Connector_USB:USB_C_Receptacle_GCT_USB4105-xx-A_16P_TopMnt_Horizontal","1",""
"R1","92.82k","","Resistor_SMD:R_0603_1608Metric","1",""
"R2","5.1","","Resistor_SMD:R_0603_1608Metric","1",""
"R3,R4,R6","100k","RC0603FR-10100KL","Resistor_SMD:R_0603_1608Metric","3",""
"R5","23.2k 1%","","Resistor_SMD:R_0603_1608Metric","1",""
"R7,R8","6.8k 1%","","Resistor_SMD:R_0603_1608Metric","2",""
"R9","182k","RC0603FR-10100KL","Resistor_SMD:R_0603_1608Metric","1",""
"R10","240R 1%","","Resistor_SMD:R_0402_1005Metric","1",""
"R11,R12","5.1k 1%","","Resistor_SMD:R_0603_1608Metric","2",""
"R13,R14","56k 1%","","Resistor_SMD:R_0603_1608Metric","2",""
"R15","5.62k 1%","","Resistor_SMD:R_0201_0603Metric","1",""
"R16","324k","RC0603FR-10100KL","Resistor_SMD:R_0603_1608Metric","1",""
"R18,R19","470k","AC0603FR-07182KL","Resistor_SMD:R_0603_1608Metric","2",""
"R21,R22,R23","1k","-- mixed values --","Resistor_SMD:R_0603_1608Metric","3",""
"SW1","BOTTOM","~","Button_Switch_SMD:SW_SPST_TL3305A","1",""
"SW2","START","~","Button_Switch_SMD:SW_SPST_TL3305A","1",""
"SW3","RESET","~","Button_Switch_SMD:SW_SPST_TL3305A","1",""
"SW4","RIGHT","~","Button_Switch_SMD:SW_SPST_TL3305A","1",""
"SW5","LEFT","~","Button_Switch_SMD:SW_SPST_TL3305A","1",""
"SW6","TOP","~","Button_Switch_SMD:SW_SPST_TL3305A","1",""
"SW7","Z","~","Button_Switch_SMD:SW_SPST_TL3305A","1",""
"SW8","Y","~","Button_Switch_SMD:SW_SPST_TL3305A","1",""
"SW9","X","~","Button_Switch_SMD:SW_SPST_TL3305A","1",""
"TP1","VBUS","~","TestPoint:TestPoint_Pad_D1.0mm","1",""
"TP2","3.3V","~","TestPoint:TestPoint_Pad_D1.0mm","1",""
"TP3","1.35V","~","TestPoint:TestPoint_Pad_D1.0mm","1",""
"TP4","1.25V","~","TestPoint:TestPoint_Pad_D1.0mm","1",""
"TP5","2.5V","~","TestPoint:TestPoint_Pad_D1.0mm","1",""
"U1","ATSAMA5D21","http://ww1.microchip.com/downloads/en/DeviceDoc/SAMA5D2-Seri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","Package_BGA:Microchip_TFBGA-196_11x11mm_Layout14x14_P0.75mm_SMD","1",""
"U2","PMIC","MCP16501TA-E/RMB","GhazanCustom:VQFN24_RMB_MCH","1",""
"U3","MT29F4G08ABAFAH4-IT:F","","GhazanCustom:BGA63C80P10X12_1050X1300X100N","1",""
"U4","AP3012","http://www.ti.com/lit/ds/symlink/tps2041.pdf","Package_TO_SOT_SMD:SOT-23-5","1",""
"Y1","12MHz","ECS-120-10-36B2-CWY-TR","Crystal:Crystal_SMD_2520-4Pin_2.5x2.0mm","1",""
"Y2","32.768kHz","ECS-.327-12.5-34B-TR","Crystal:Crystal_SMD_3215-2Pin_3.2x1.5mm","1",""

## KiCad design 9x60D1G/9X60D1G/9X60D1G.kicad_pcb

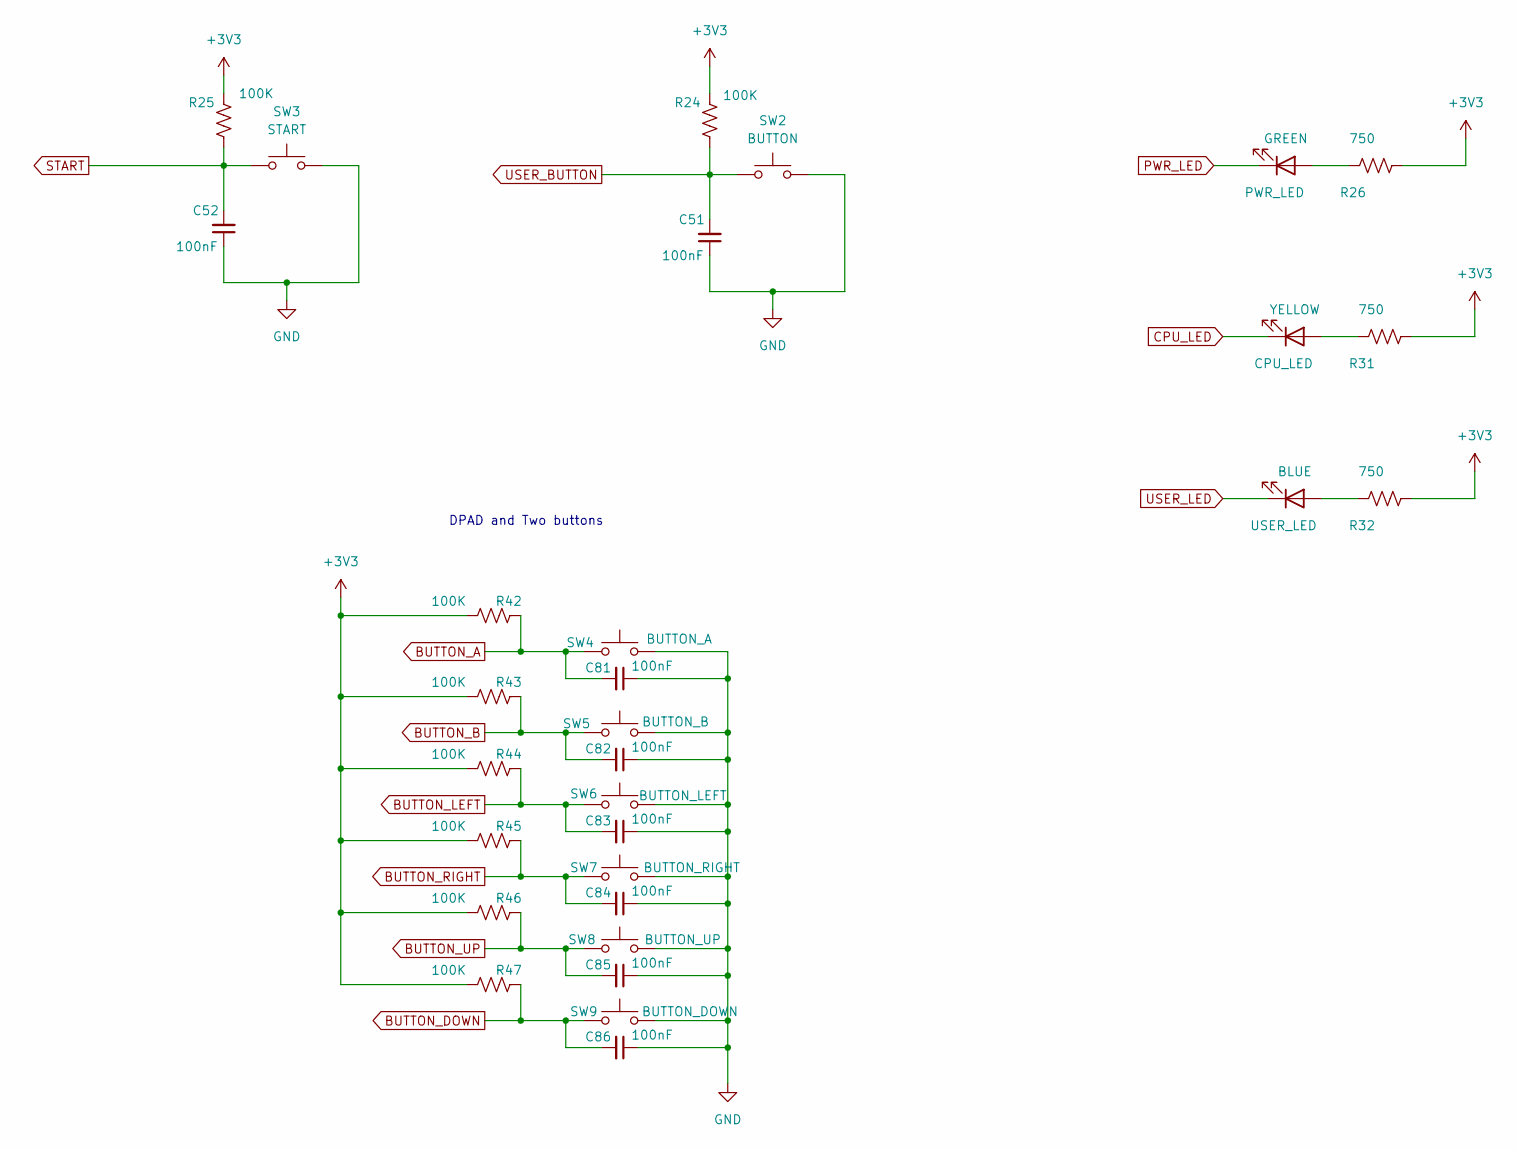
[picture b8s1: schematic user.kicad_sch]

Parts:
C51, C52, C81, C82, C83, C84, C85, C86: 100nF; C_0805_2012Metric
D1: PWR_LED; LED_0805_2012Metric
D2: CPU_LED; LED_0805_2012Metric
D3: USER_LED; LED_0805_2012Metric
R24, R25, R42, R43, R44, R45, R46, R47: 100K; R_0805_2012Metric
R26, R31, R32: 750; R_0805_2012Metric
SW2: BUTTON; SW_Push_1P1T_NO_6x6mm_H9.5mm
SW3: START; SW_Push_1P1T_NO_6x6mm_H9.5mm
SW4: BUTTON_A; SW_Push_1P1T_NO_6x6mm_H9.5mm
SW5: BUTTON_B; SW_Push_1P1T_NO_6x6mm_H9.5mm
SW6: BUTTON_LEFT; SW_Push_1P1T_NO_6x6mm_H9.5mm
SW7: BUTTON_RIGHT; SW_Push_1P1T_NO_6x6mm_H9.5mm
SW8: BUTTON_UP; SW_Push_1P1T_NO_6x6mm_H9.5mm
SW9: BUTTON_DOWN; SW_Push_1P1T_NO_6x6mm_H9.5mm

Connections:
+3V3: R24.1, R25.1, R26.2, R31.2, R32.2, R42.1, R43.1, R44.1, R45.1, R46.1, R47.1; also elsewhere on the board
BUTTON_A: C81.2, R42.2, SW4.1; also elsewhere on the board
BUTTON_B: C82.2, R43.2, SW5.1; also elsewhere on the board
BUTTON_DOWN: C86.2, R47.2, SW9.1; also elsewhere on the board
BUTTON_LEFT: C83.2, R44.2, SW6.1; also elsewhere on the board
BUTTON_RIGHT: C84.2, R45.2, SW7.1; also elsewhere on the board
BUTTON_UP: C85.2, R46.2, SW8.1; also elsewhere on the board
CPU_LED: D2.1 (K); also elsewhere on the board
GND: C51.1, C52.1, C81.1, C82.1, C83.1, C84.1, C85.1, C86.1, SW2.2, SW3.2, SW4.2, SW5.2, SW6.2, SW7.2, SW8.2, SW9.2; also elsewhere on the board
unnamed: D1.2 (A), R26.1
unnamed: D2.2 (A), R31.1
unnamed: D3.2 (A), R32.1
PWR_LED: D1.1 (K); also elsewhere on the board
START: C52.2, R25.2, SW3.1; also elsewhere on the board
USER_BUTTON: C51.2, R24.2, SW2.1; also elsewhere on the board
USER_LED: D3.1 (K); also elsewhere on the board

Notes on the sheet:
DPAD and Two buttons
